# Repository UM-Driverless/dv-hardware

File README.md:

# dv-hardware

Hardware (KiCad) projects for the Driverless section of U-Motorsport (URJC Formula Student).

Firmware lives in [UM-Driverless/kart-medulla](https://github.com/UM-Driverless/kart-medulla). Pair board revisions with firmware releases via matching git tags (e.g. `medulla-v1.2` here, `medulla-v1.2-fw` there).

## Layout
```
lib/                 shared symbols, footprints, 3D models — referenced by every project
projects/<board>/    one folder per board (KiCad project, EasyEDA source archive,
                     the board's requirements.md, tasks.md and docs/)
tasks.md             cross-board tasks + the index of every per-board task board
fab/<board>/<rev>/   released Gerbers, BOM, pick-and-place, JLC zip
docs/                cross-board notes
.agents/             agent-readable project knowledge (history, errors)
```

## Board identity
A manufactured board is identified by the commit in this repo that its gerbers were exported from,
written on the board as a QR code or label (short hash is enough). Firmware repos quote that hash to
declare which hardware they target. Because rework exists on a physical board and in no commit, each
board also carries a rework list alongside its hash. Worked example and the boards that exist:
[`projects/kart-medulla/README.md`](projects/kart-medulla/README.md).

## Migration status
Projects originate in EasyEDA Pro and are being migrated to KiCad 9. Each `projects/<board>/` keeps:
- `easyeda-source/` — original `.epro` exports for reference (do not edit)
- `<board>.kicad_pro` (and friends) — the live KiCad project after import

## First-time setup

Install **KiCad 10.x** with the **3D shapes** package included (default in the official installer). The boards reference `${KICAD10_3DMODEL_DIR}` for standard parts (caps, resistors, SOIC, SOT, headers, …); without that variable set, the 3D viewer comes up empty.

After installing, verify the path:

- macOS: `KiCad → Settings… → Configure Paths…` → row `KICAD10_3DMODEL_DIR` should point to `/Applications/KiCad/KiCad.app/Contents/SharedSupport/3dmodels`
- Linux: `/usr/share/kicad/3dmodels`
- Windows: `C:\Program Files\KiCad\10.0\share\kicad\3dmodels`

Project-specific 3D models (parts not in KiCad's standard library — connectors, the MAX4660, …) live next to the board under `projects/<board>/3dmodels/` and are referenced via `${KIPRJMOD}/3dmodels/...` so they travel with the repo.

## Workflow
1. `git pull --rebase` before starting work.
2. One person per board at a time — coordinate in chat. KiCad files are text but not line-mergeable.
3. Commit small, commit often.
4. Run `kicad-cli sch erc` and `kicad-cli pcb drc` before fab. CI does this automatically (TODO).

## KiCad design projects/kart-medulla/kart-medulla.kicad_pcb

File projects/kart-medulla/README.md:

# kart-medulla

PCB pairs with the firmware in [UM-Driverless/kart-medulla](https://github.com/UM-Driverless/kart-medulla).

Originally called "ESP32 Expander" in EasyEDA (Jan 2026), renamed to "Kart Medulla (expander for ESP 32)" in May 2026. Both EasyEDA exports kept under `easyeda-source/` for diff history.

## Board identity

**A manufactured board is identified by the dv-hardware commit its gerbers were exported from**,
written on the board as a QR code or label — short form is enough, e.g. `84d6dd0`. Firmware repos
quote that hash to say which hardware they target, so "does this code match this board?" is a
question anyone can answer by reading the board.

Use the **gerber-export** commit, not the last commit that touched the schematic. They are usually
different, and only the export is what a fab house ever received.

**A board stops matching its hash the moment it is reworked.** The hash names the design it was made
from; a lifted pin or a patch wire exists on that one physical board and in no commit. So each board
also carries a rework list below. A rework entry may name the commit whose behaviour it brings the
board up to — that is how a patched board gets described precisely without inventing a new
identifier for it.

### Boards in existence

**`84d6dd0`** — "medulla: add fabrication gerbers + drill files (zip for fab)". The last commit
touching `fabrication/`, so it is the best available evidence of what the fab house received;
inferred from this repo rather than read off a purchase order. Paired with kart-brain `main` at
`c200e56`. Also reachable as the git tag `kart-medulla-v1`, which is only an alias — the hash is
what the board carries and what firmware quotes.

Two pins are also used for something other than their designed signal on this board (the steering
sensor's PWM on `PRESSURE_3`, the compressor MOSFET gate on `BUZZER`) — that is firmware assignment
rather than copper, so it is listed in
[`docs/pinout-kart-medulla-v1.md`](docs/pinout-kart-medulla-v1.md) under "As-built pin use". Read both that section
and the list below to know what this board actually does.

Rework outstanding on this board:

- **CN10.2 brake output is on the wrong side of the LM358.** The board carries the unamplified 0-5 V
  DAC output where the valve needs 0-10 V, and the U13.10 -> U1.3 copper (DAC to amplifier input) is
  unrouted. Fixed in the design by `f68cc1f`, which is *after* this board was made, so the board
  still has the fault. Needs a physical patch — see [`tasks.md`](tasks.md).
- **R10 removed, to read the steering sensor's PWM on GPIO 1.** The `PRESSURE_3` front end is
  `CN5.2 —[R8 10k]— node —[R9 10k]— GPIO 1 —[R10 10k]— GND`. R10 is the only shunt to ground, so
  removing it (and only it) turns the terminal into a usable digital input; R8 + R9 stay as a 20 kΩ
  series, which is far too high-impedance for the ADC — that is why this pin is decoded as PWM with
  the MCPWM capture peripheral rather than read as an analog voltage. Recorded here 2026-07-31; the
  reasoning and the wiring context are on the kart-docs medulla page.
- **Check for abandoned throttle-bypass rework.** The working throttle path uses MCP4922 channel A:
  a 2026-08-08 workshop video records it working with the “new DAC chip at 5 volts,” and the kart
  later accelerated on command under remote control. The record does not establish whether the
  original chip was faulty or exactly when it was changed.
  The temporary GPIO 38 filtered-PWM firmware path was reverted. Inspect this physical board for a
  leftover flying wire from GPIO 38 toward U14 pin 8 and confirm U13 pin 14 was not left lifted; remove
  the wire and restore the pin if either change was ever soldered. See the firmware repo's `tasks.md`.

## Migration status (2026-05-03)
Converted via [ConvertEDA](https://converteda.com) from EasyEDA Pro 2.2.47.7. KiCad 10.0.1's built-in `Import Non-KiCad Project → EasyEDA Pro` silently failed on this `.epro` (produced empty stubs) — likely a format-version lag against EasyEDA Pro 2.2.47.x. ConvertEDA handled it cleanly.

Renamed all internal references from `Kart_Medulla_(expander_for_ESP_32)` to `kart-medulla` (file names, sheet refs, project name, title block) for consistency with the firmware repo.

### Known cleanup needed (raw conversion baseline)
- 347 ERC violations: mostly missing `gen` symbol library (converter creates `gen:` lib_id refs but doesn't ship the library), `power` library mismatches (`12V`, `+5V_REG` not in KiCad's stdlib power), missing `fp-lib-table`.
- 165 DRC violations + 31 unconnected items: expected until footprint library is registered and net ties verified.

Cleanup work tracked separately. The current commit is the as-converted baseline so future cleanup commits show a clean diff.

## Fonts

Silkscreen text on the PCB uses **DejaVu Sans Mono**. There is no monospace font shared by default between macOS and Ubuntu, so contributors must install it locally:

- **Ubuntu:** ships by default — no action needed.
- **macOS:** `brew install --cask font-dejavu` then restart KiCad.

Alternatively, `File → Board Setup → Embedded Files` lets KiCad embed the font into the .kicad_pcb so it travels with the project. See `history.md` 2026-05-09 entry for details.

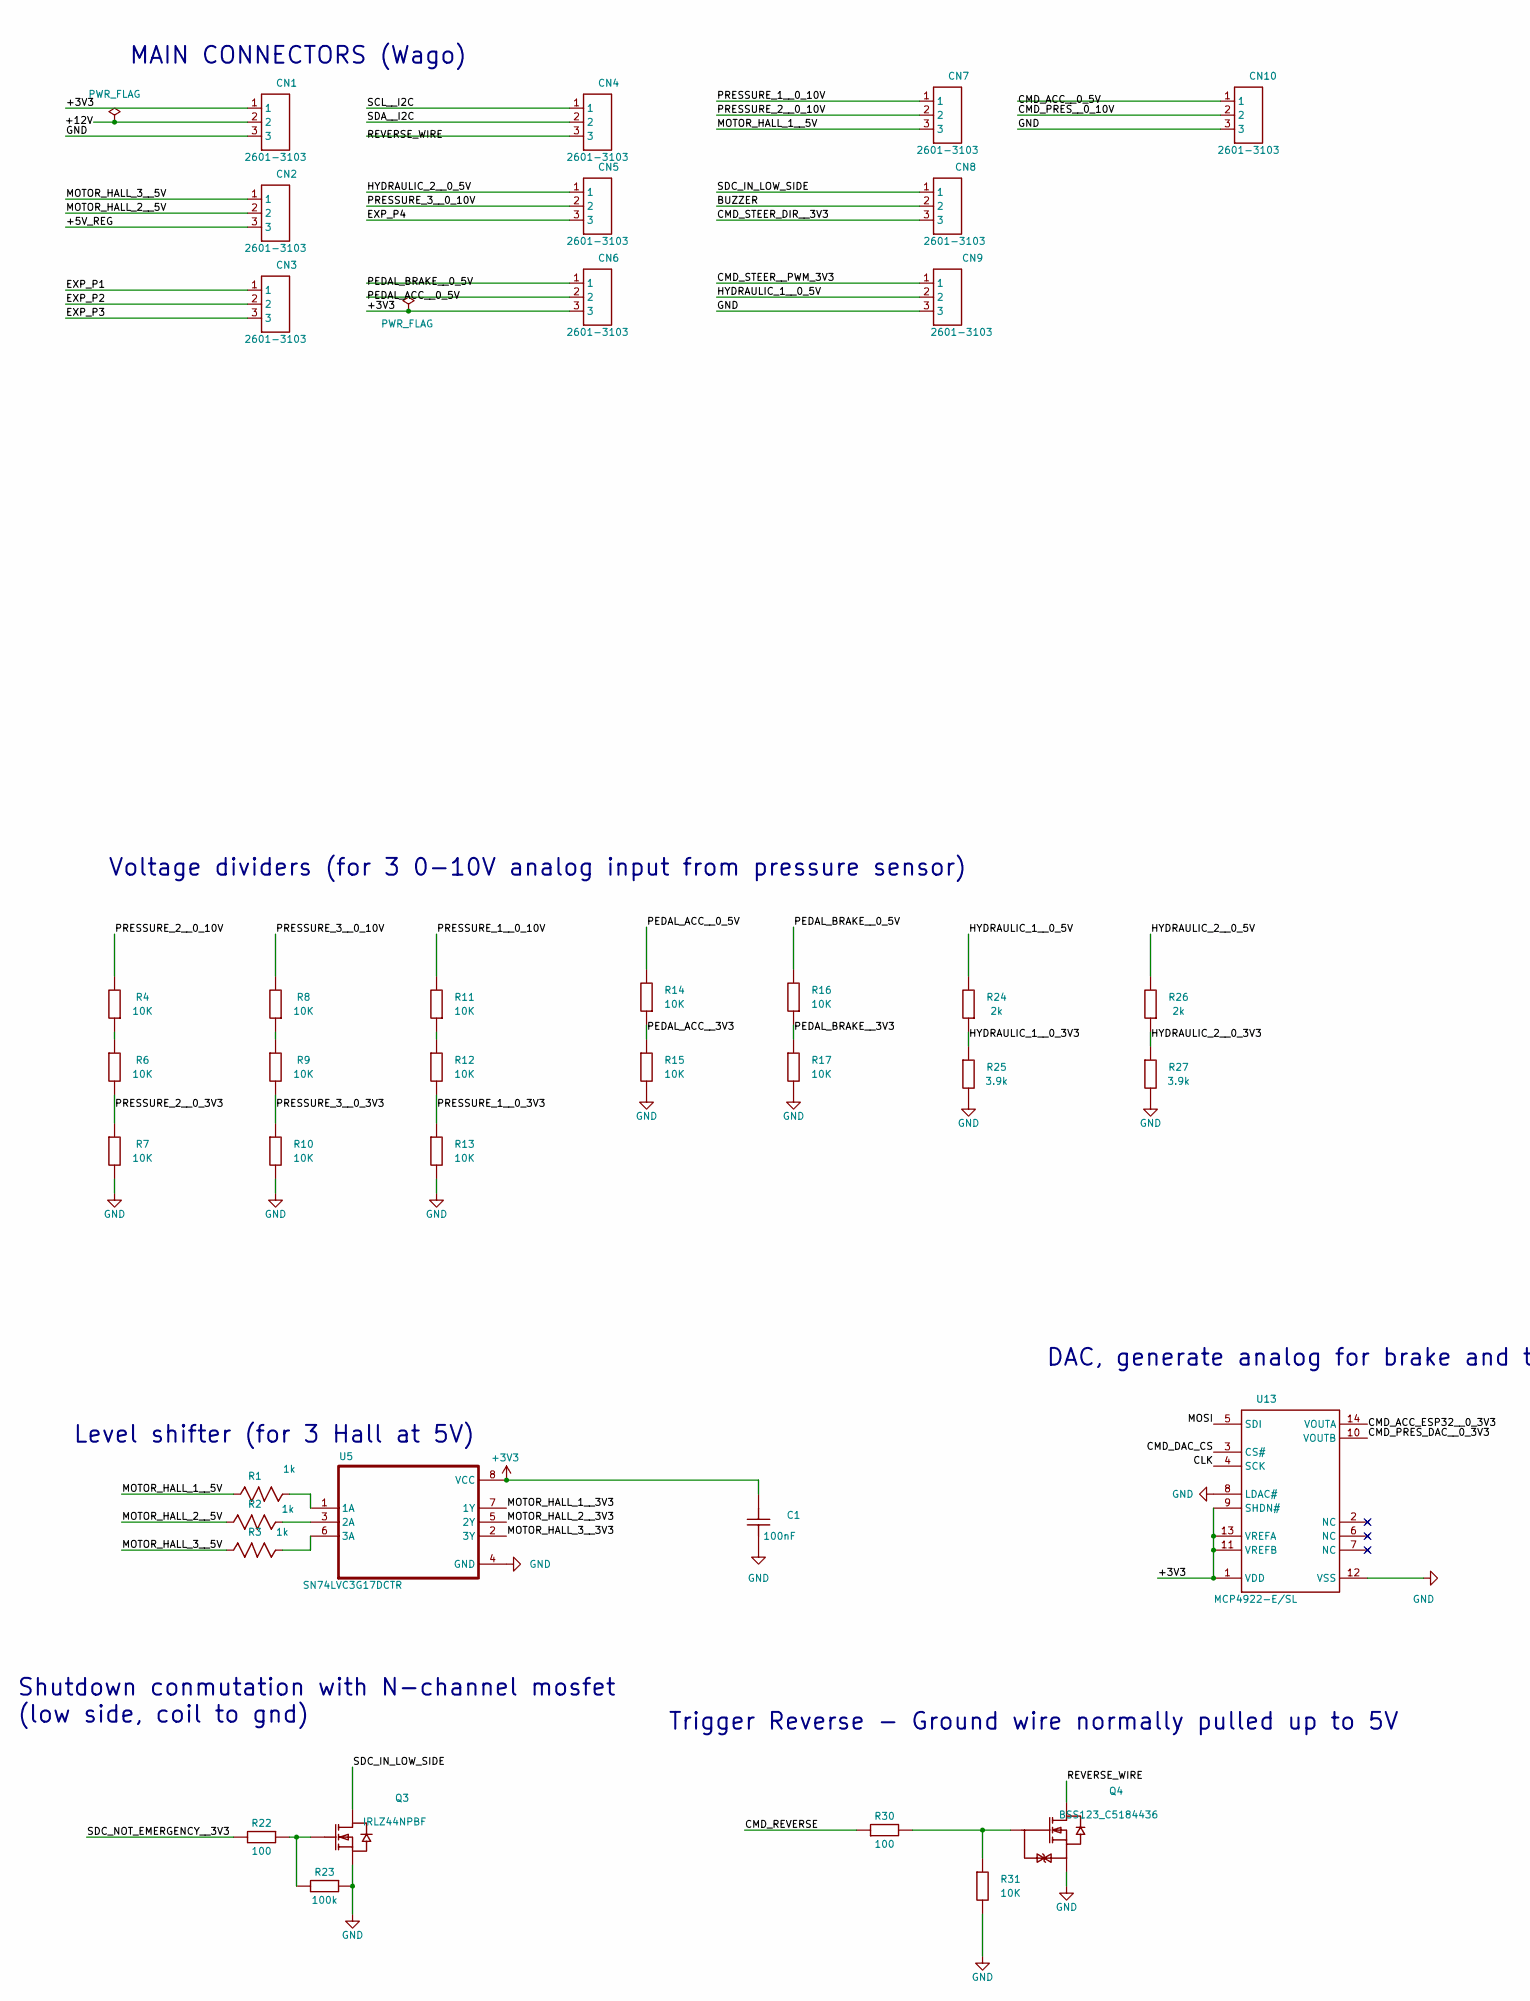
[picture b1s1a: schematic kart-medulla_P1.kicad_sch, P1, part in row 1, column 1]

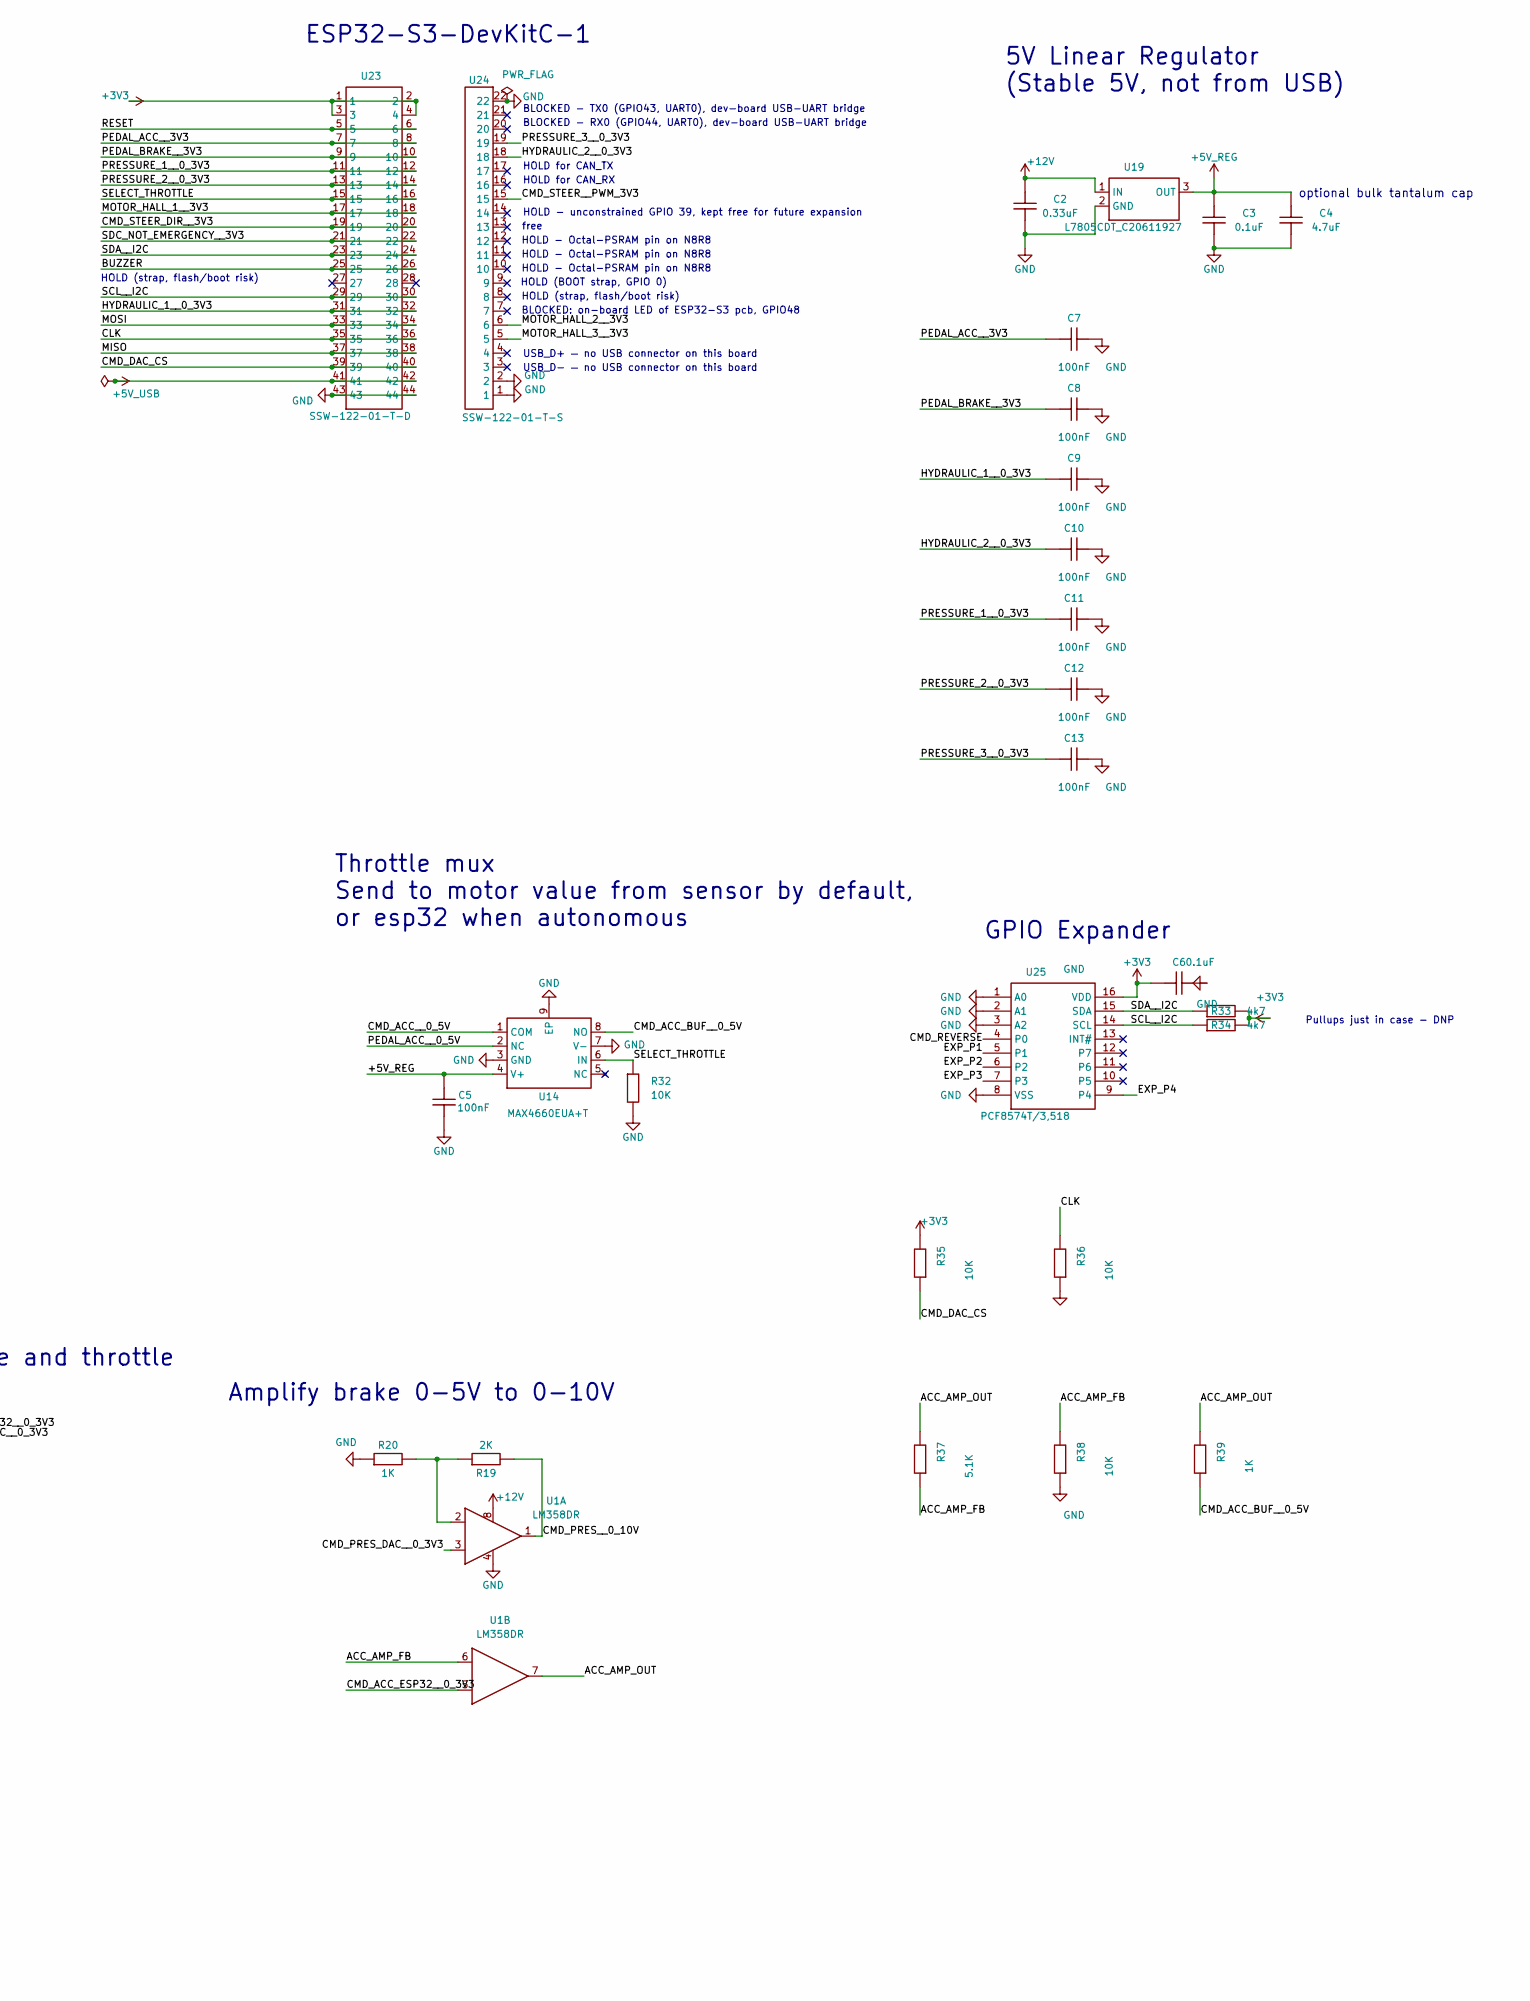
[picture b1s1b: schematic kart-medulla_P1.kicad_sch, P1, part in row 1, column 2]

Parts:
C1: 100nF; C0603; part_bbox -10.5,-8.5,10.5,8.5
C2: 0.33uF; C0603; part_bbox -10,8,10,-8
C3, C6: 0.1uF; C0603; part_bbox -10,8,10,-8
C4: 4.7uF; C0603; part_bbox -10,8,10,-8
C5: 100nF; C0603; part_bbox -10,8,10,-8
C7, C8, C9, C10, C11, C12, C13: 100nF; C0603
CN1, CN2, CN3, CN4, CN5, CN6, CN7, CN8, CN9, CN10: 2601-3103; TerminalBlock_WAGO_2601-3103_1x03_P3.50mm_Vertical; part_bbox -10,-20,10,20
Q3: IRLZ44NPBF; TO-220-3_L10.0-W4.5-P2.54-T; part_bbox -10.5,-10.5,24.5,10.5
Q4: BSS123_C5184436; SOT-23_L2.9-W1.3-P1.90-LS2.4-BR; part_bbox -22.5,-13.5,23.5,20.5
R1, R2, R3: 1k; R0603; part_bbox -15.5,-5.5,15.5,5.5
R4, R6, R7, R8, R9, R10, R11, R12, R13, R14, R15, R16, R17, R31, R32: 10K; R0603; part_bbox -10,4,10,-4
R19: 2K; R0603; part_bbox -10,4,10,-4
R20: 1K; R0603; part_bbox -10,4,10,-4
R22, R30: 100; R0603; part_bbox -10,4,10,-4
R23: 100k; R0603; part_bbox -10,4,10,-4
R24, R26: 2k; R0603; part_bbox -10,4,10,-4
R25, R27: 3.9k; R0603; part_bbox -10,4,10,-4
R33, R34: 4k7; R0603; part_bbox -10,4,10,-4
R35, R36, R38: 10K; R0603
R37: 5.1K; R0603
R39: 1K; R0603
U1: LM358DR; SOIC-8_L5.0-W4.0-P1.27-LS6.0-BL; part_bbox -21,-22.69999999999999,21,21
U5: SN74LVC3G17DCTR; SOP65P400X130-8N; part_bbox -50,40,50,-40
U13: MCP4922-E/SL; SOIC-14_L8.7-W3.9-P1.27-LS6.0-BL; Manufacturer Part MCP4922-E/SL; JLCPCB Part Class Extended Part
U14: MAX4660EUA+T; SOP65P490X110-9N; part_bbox -25,-25,35,25
U19: L7805CDT_C20611927; TO-252-2_L6.6-W6.1-P4.57-LS9.9-BR-CW; part_bbox -20,-20,30,10
U23: SSW-122-01-T-D; HDR-TH_ESQ-122-59-G-D; part_bbox -20,-110,20,120
U24: SSW-122-01-T-S; HDR-TH_ESQ-122-23-G-S; part_bbox -10,-115,10,115
U25: PCF8574T/3,518; SOIC-16_3.9x9.9mm_P1.27mm; part_bbox -30,-45,30,45

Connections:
+3V3: C1.1, C6.2, CN1.1, CN6.3, R33.2, R34.2, R35.2, U5.8 (VCC), U13.1 (VDD), U13.9 (SHDN#), U13.11 (VREFB), U13.13 (VREFA), U23.1, U23.2, U23.3, U23.4, U25.16 (VDD)
+5V_REG: C3.2, C4.2, C5.2, CN2.3, U14.4 (V+), U19.3 (OUT)
+5V_USB: U23.41, U23.42
+12V: C2.2, CN1.2, U1.8 (+V), U19.1 (IN)
/P1/ACC_AMP_FB: R37.1, R38.2, U1.6 (-IN2)
/P1/ACC_AMP_OUT: R37.2, R39.2, U1.7 (OUT2)
/P1/BUZZER: CN8.2, U23.25, U23.26
/P1/CLK: R36.2, U13.4 (SCK), U23.35, U23.36
/P1/CMD_ACC_BUF__0_5V: R39.1, U14.8 (NO)
/P1/CMD_ACC_ESP32__0_3V3: U1.5 (+IN2), U13.14 (VOUTA)
/P1/CMD_ACC__0_5V: CN10.1, U14.1 (COM)
/P1/CMD_DAC_CS: R35.1, U13.3 (CS#), U23.39, U23.40
/P1/CMD_PRES_DAC__0_3V3: U1.3 (+IN1), U13.10 (VOUTB)
/P1/CMD_PRES__0_10V: CN10.2, R19.2, U1.1 (OUT1)
/P1/CMD_REVERSE: R30.1, U25.4 (P0)
/P1/CMD_STEER_DIR__3V3: CN8.3, U23.19, U23.20
/P1/CMD_STEER__PWM_3V3: CN9.1, U24.15
/P1/EXP_P1: CN3.1, U25.5 (P1)
/P1/EXP_P2: CN3.2, U25.6 (P2)
/P1/EXP_P3: CN3.3, U25.7 (P3)
/P1/EXP_P4: CN5.3, U25.9 (P4)
/P1/HYDRAULIC_1__0_3V3: C9.2, R24.1, R25.1, U23.31, U23.32
/P1/HYDRAULIC_1__0_5V: CN9.2, R24.2
/P1/HYDRAULIC_2__0_3V3: C10.2, R26.1, R27.1, U24.18
/P1/HYDRAULIC_2__0_5V: CN5.1, R26.2
/P1/MISO: U23.37, U23.38
/P1/MOSI: U13.5 (SDI), U23.33, U23.34
/P1/MOTOR_HALL_1__3V3: U5.7 (1Y), U23.17, U23.18
/P1/MOTOR_HALL_1__5V: CN7.3, R1.1
/P1/MOTOR_HALL_2__3V3: U5.5 (2Y), U24.6
/P1/MOTOR_HALL_2__5V: CN2.2, R2.1
/P1/MOTOR_HALL_3__3V3: U5.2 (3Y), U24.5
/P1/MOTOR_HALL_3__5V: CN2.1, R3.1
/P1/PEDAL_ACC__0_5V: CN6.2, R14.2, U14.2 (NC)
/P1/PEDAL_ACC__3V3: C7.2, R14.1, R15.1, U23.7, U23.8
/P1/PEDAL_BRAKE__0_5V: CN6.1, R16.2
/P1/PEDAL_BRAKE__3V3: C8.2, R16.1, R17.1, U23.9, U23.10
/P1/PRESSURE_1__0_3V3: C11.2, R12.2, R13.1, U23.11, U23.12
/P1/PRESSURE_1__0_10V: CN7.1, R11.2
/P1/PRESSURE_2__0_3V3: C12.2, R6.2, R7.1, U23.13, U23.14
/P1/PRESSURE_2__0_10V: CN7.2, R4.2
/P1/PRESSURE_3__0_3V3: C13.2, R9.2, R10.1, U24.19
/P1/PRESSURE_3__0_10V: CN5.2, R8.2
/P1/RESET: U23.5, U23.6
/P1/REVERSE_WIRE: CN4.3, Q4.3 (D)
/P1/SCL__I2C: CN4.1, R34.1, U23.29, U23.30, U25.14 (SCL)
/P1/SDA__I2C: CN4.2, R33.1, U23.23, U23.24, U25.15 (SDA)
/P1/SDC_IN_LOW_SIDE: CN8.1, Q3.2 (D)
/P1/SDC_NOT_EMERGENCY__3V3: R22.2, U23.21, U23.22
/P1/SELECT_THROTTLE: R32.1, U14.6 (IN), U23.15, U23.16
GND: C1.2, C2.1, C3.1, C4.1, C5.1, C6.1, C7.1, C8.1, C9.1, C10.1, C11.1, C12.1, C13.1, CN1.3, CN9.3, CN10.3, Q3.3 (S), Q4.2 (S), R7.2, R10.2, R13.2, R15.2, R17.2, R20.1, R23.1, R25.2, R27.2, R31.2, R32.2, R36.1, R38.1, U1.4 (GND), U5.4 (GND), U13.8 (LDAC#), U13.12 (VSS), U14.3 (GND), U14.7 (V-), U14.9 (EP), U19.2 (GND), U23.43, U23.44, U24.1, U24.2, U24.22, U25.1 (A0), U25.2 (A1), U25.3 (A2), U25.8 (VSS)
unnamed: Q3.1 (G), R22.1, R23.2
unnamed: Q4.1 (G), R30.2, R31.1
unnamed: R4.1, R6.1
unnamed: R8.1, R9.1
unnamed: R11.1, R12.1
unnamed: R19.1, R20.2, U1.2 (-IN1)
unnamed: R1.2, U5.1 (1A)
unnamed: R2.2, U5.3 (2A)
unnamed: R3.2, U5.6 (3A)

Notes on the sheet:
Pullups just in case - DNP
GPIO Expander
Level shifter (for 3 Hall at 5V)
Trigger Reverse - Ground wire normally pulled up to 5V
optional bulk tantalum cap
ESP32-S3-DevKitC-1
HOLD for CAN_TX
Shutdown conmutation with N-channel mosfet (low side, coil to gnd)
USB_D- — no USB connector on this board
HOLD - Octal-PSRAM pin on N8R8
DAC, generate analog for brake and throttle
Amplify brake 0-5V to 0-10V
HOLD for CAN_RX
HOLD (strap, flash/boot risk)
MAIN CONNECTORS (Wago)
HOLD (BOOT strap, GPIO 0)
BLOCKED - TX0 (GPIO43, UART0), dev-board USB-UART bridge
BLOCKED - RX0 (GPIO44, UART0), dev-board USB-UART bridge
BLOCKED: on-board LED of ESP32-S3 pcb, GPIO48
free
Voltage dividers (for 3 0-10V analog input from pressure sensor)
USB_D+ — no USB connector on this board
HOLD - unconstrained GPIO 39, kept free for future expansion
Throttle mux Send to motor value from sensor by default, or esp32 when autonomous
5V Linear Regulator (Stable 5V, not from USB)

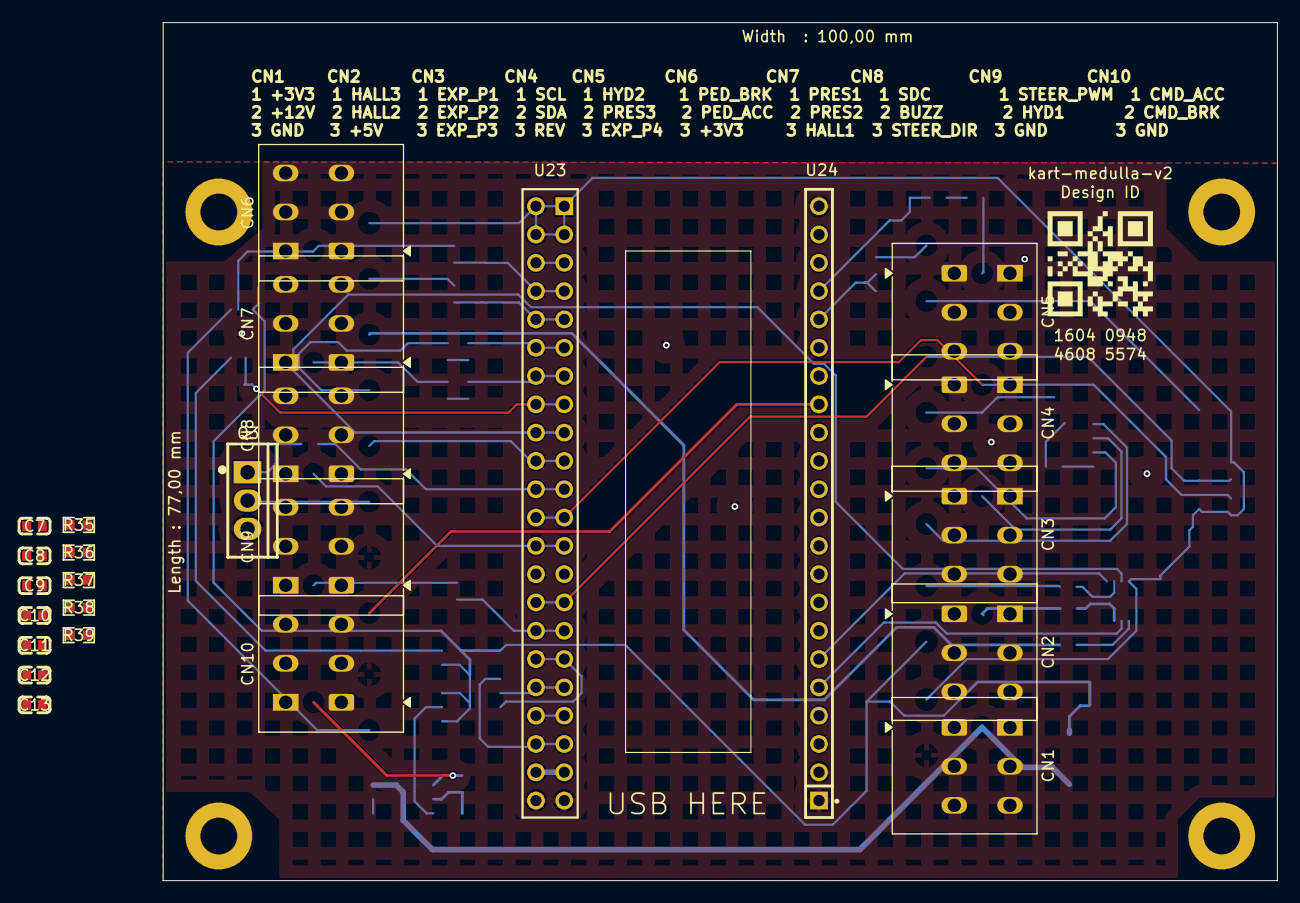
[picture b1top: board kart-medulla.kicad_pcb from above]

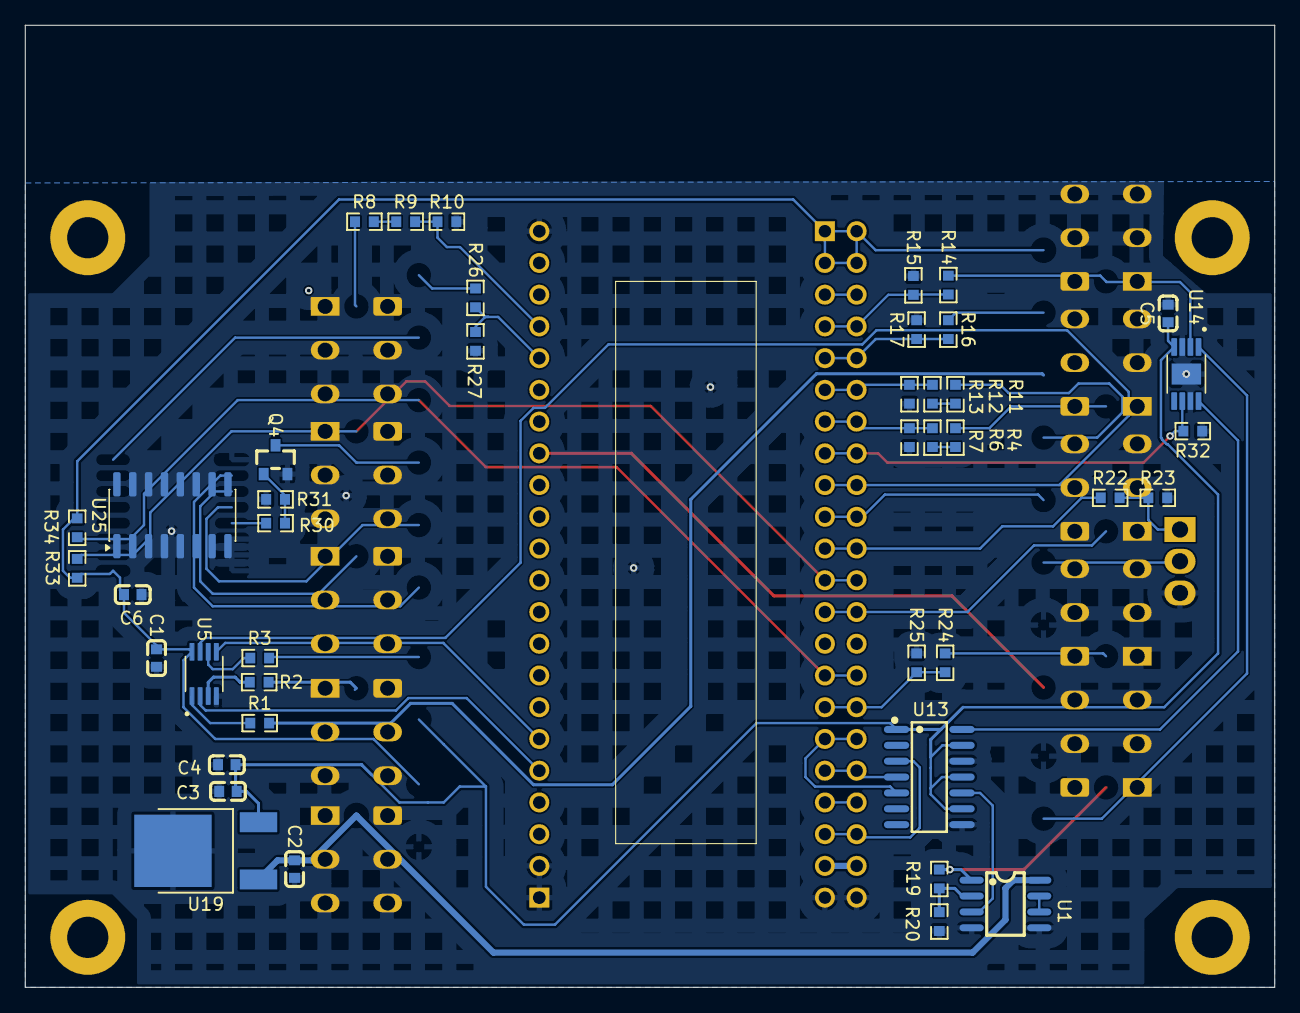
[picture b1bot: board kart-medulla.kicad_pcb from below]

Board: 2 copper layers, 100.0 x 77.0 mm, 71 parts (42 on the bottom side), 60 nets.

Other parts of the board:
PAD1: single_pad; standalone_pad_0001
PAD2: single_pad; standalone_pad_0002
PAD3: single_pad; standalone_pad_0003
PAD4: single_pad; standalone_pad_0004

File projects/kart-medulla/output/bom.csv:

"Reference","Value","Footprint","QUANTITY","DNP"
"C1,C5,C7-C13","100nF","kart-medulla:C0603","9",""
"C2","0.33uF","kart-medulla:C0603","1",""
"C3,C6","0.1uF","kart-medulla:C0603","2",""
"C4","4.7uF","kart-medulla:C0603","1",""
"CN1-CN10","2601-3103","kart-medulla:TerminalBlock_WAGO_2601-3103_1x03_P3.50mm_Vertical","10",""
"Q3","IRLZ44NPBF","kart-medulla:TO-220-3_L10.0-W4.5-P2.54-T","1",""
"Q4","BSS123_C5184436","kart-medulla:SOT-23_L2.9-W1.3-P1.90-LS2.4-BR","1",""
"R1-R3","1k","kart-medulla:R0603","3",""
"R4,R6-R17,R31,R32,R35,R36,R38","10K","kart-medulla:R0603","18",""
"R19","2K","kart-medulla:R0603","1",""
"R20,R39","1K","kart-medulla:R0603","2",""
"R22,R30","100","kart-medulla:R0603","2",""
"R23","100k","kart-medulla:R0603","1",""
"R24,R26","2k","kart-medulla:R0603","2",""
"R25,R27","3.9k","kart-medulla:R0603","2",""
"R33,R34","4k7","kart-medulla:R0603","2",""
"R37","5.1K","kart-medulla:R0603","1",""
"U1","LM358DR","kart-medulla:SOIC-8_L5.0-W4.0-P1.27-LS6.0-BL","1",""
"U5","SN74LVC3G17DCTR","kart-medulla:SOP65P400X130-8N","1",""
"U13","MCP4922-E/SL","kart-medulla:SOIC-14_L8.7-W3.9-P1.27-LS6.0-BL","1",""
"U14","MAX4660EUA+T","kart-medulla:SOP65P490X110-9N","1",""
"U19","L7805CDT_C20611927","kart-medulla:TO-252-2_L6.6-W6.1-P4.57-LS9.9-BR-CW","1",""
"U23","SSW-122-01-T-D","kart-medulla:HDR-TH_ESQ-122-59-G-D","1",""
"U24","SSW-122-01-T-S","kart-medulla:HDR-TH_ESQ-122-23-G-S","1",""
"U25","PCF8574T/3,518","Package_SO:SOIC-16_3.9x9.9mm_P1.27mm","1",""

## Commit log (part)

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2026-05-03 history: log gitignore trailing-comment gotcha
2026-05-07 First commit with github app
2026-05-07 few errors left
2026-05-07 pcb headers lock
2026-05-07 headers lock update
2026-05-07 trying to fix schematic
2026-05-07 Nonsense error fixed, i dont know how
2026-05-07 Fix all ERC errors
2026-05-07 pcb update
2026-05-07 agents: update tasks, error-log, AGENTS
2026-05-07 kart-medulla: schematic updates and docs
2026-05-07 add buffer circuit on second opamp to remove noise
2026-05-07 lock_esp32headers
2026-05-07 kart-medulla: PCB↔schematic resync + agent workflow rules
    PCB sync (the original goal — get ratsnest/Nets count right):
    - Update PCB from Schematic with "Re-link footprints by reference"
    to repair empty symbol associations on every PCB footprint. Brings
    net count from 34 → ~80, ratsnest now populates correctly.
    - Adds CN9, CN10 footprints that existed in schematic but not PCB.
    - Footprint library names normalized to kart-medulla:* prefix.
2026-05-08 Fix duplicate signal mess
2026-05-08 schematic ok
2026-05-08 pcb ok
2026-05-08 error-log: simpler git advice rule
2026-05-08 pcb until nets update
2026-05-08 error-log: common-sense lapses pattern
2026-05-08 pcb in progress
2026-05-08 pcb routes update
2026-05-08 refilled update
2026-05-09 Adjustments to layers and holes
2026-05-09 logo and connections
